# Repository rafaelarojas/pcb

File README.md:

# Placa de circuito impresso com Raspberry Pi Pico

Esta atividade tem por objetivo desenvolver uma placa de circuito impresso capaz de receber um Raspberry Pi Pico W encaixado utilizando um dispositivo conector, além de um hardware para acionar uma interface de potência (relé e transistor), um dispositivo sinalizador (LED ou Buzzer) e um dispositivo de entrada (analógico ou digital). Esta placa deverá ser construída utilizando o software de CAD para placas eletrônicas utilizado no módulo vigente. O software utilizado foi o KiCad.

## Arquivos

Dentro da pasta `projeto` é possível encontrar os arquívos `projeto.kicad_pcb` que se encontra a pcb do projeto, `projeto.kicad_prl`, `projeto.kicad_pro`, `projeto.kicad_sch` do esquema, `~projeto.kicad_pcb.lck`

## PCB

<p align="center">

## Schema

<p align="center">

## 3D

<p align="center">

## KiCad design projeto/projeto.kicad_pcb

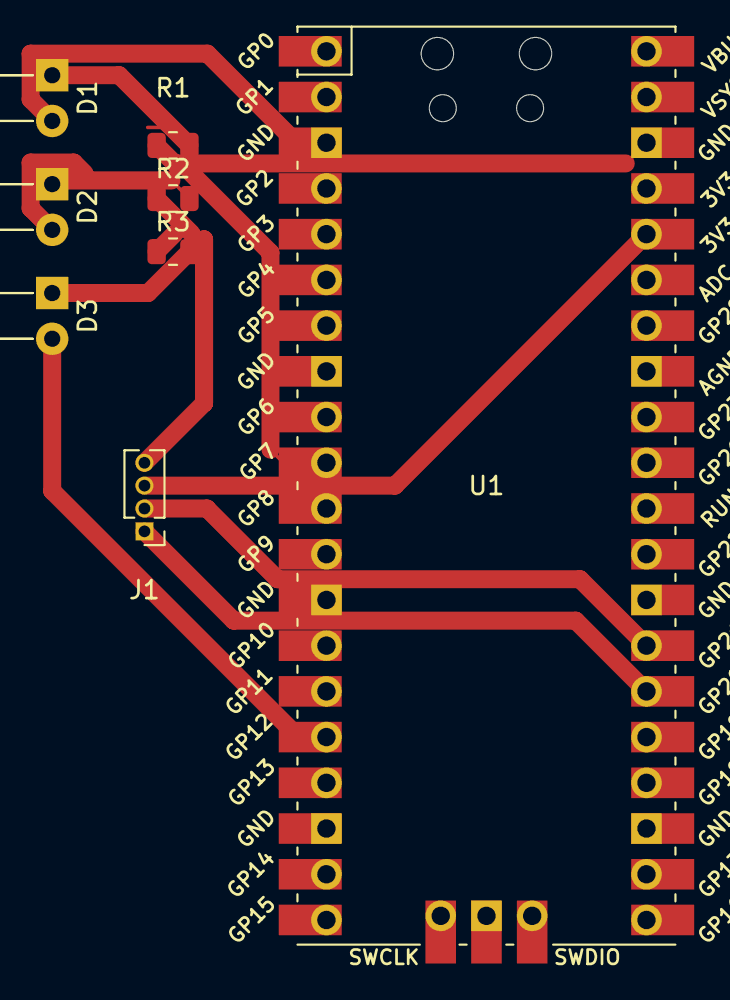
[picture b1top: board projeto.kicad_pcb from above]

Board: 2 copper layers, 8 parts (0 on the bottom side), 3 nets.

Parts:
D1, D2, D3: LED; LED_D3.0mm_Horizontal_O6.35mm_Z10.0mm
J1: Conn_01x04_Pin; PinHeader_1x04_P1.27mm_Vertical
R1, R2, R3: 220R; R_0805_2012Metric
U1: Pico; RPi_Pico_SMD_TH

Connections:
unnamed: D3.2 (A), U1.15 (GPIO11), U1.16 (GPIO12)
unnamed: J1.1, J1.2, U1.12 (GPIO9), U1.13 (GND), U1.26 (GPIO20), U1.27 (GPIO21)
unnamed: D1.1 (K), D1.2 (A), D2.1 (K), D2.2 (A), D3.1 (K), J1.3, J1.4, R1.1, R1.2, R2.1, R2.2, R3.1, R3.2, U1.2 (GPIO1), U1.3 (GND), U1.5 (GPIO3), U1.6 (GPIO4), U1.7 (GPIO5), U1.8 (GND), U1.9 (GPIO6), U1.10 (GPIO7), U1.11 (GPIO8), U1.36 (3V3), U1.38 (GND)

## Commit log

2024-03-28 add project
